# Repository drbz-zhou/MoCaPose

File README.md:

Reference:
@article{zhou2023mocapose,
  title={Mocapose: Motion capturing with textile-integrated capacitive sensors in loose-fitting smart garments},
  author={Zhou, Bo and Geissler, Daniel and Faulhaber, Marc and Gleiss, Clara Elisabeth and Zahn, Esther Friederike and Ray, Lala Shakti Swarup and Gamarra, David and Rey, Vitor Fortes and Suh, Sungho and Bian, Sizhen and others},
  journal={Proceedings of the ACM on Interactive, Mobile, Wearable and Ubiquitous Technologies},
  volume={7},
  number={1},
  pages={1--40},
  year={2023},
  publisher={ACM New York, NY, USA}
}

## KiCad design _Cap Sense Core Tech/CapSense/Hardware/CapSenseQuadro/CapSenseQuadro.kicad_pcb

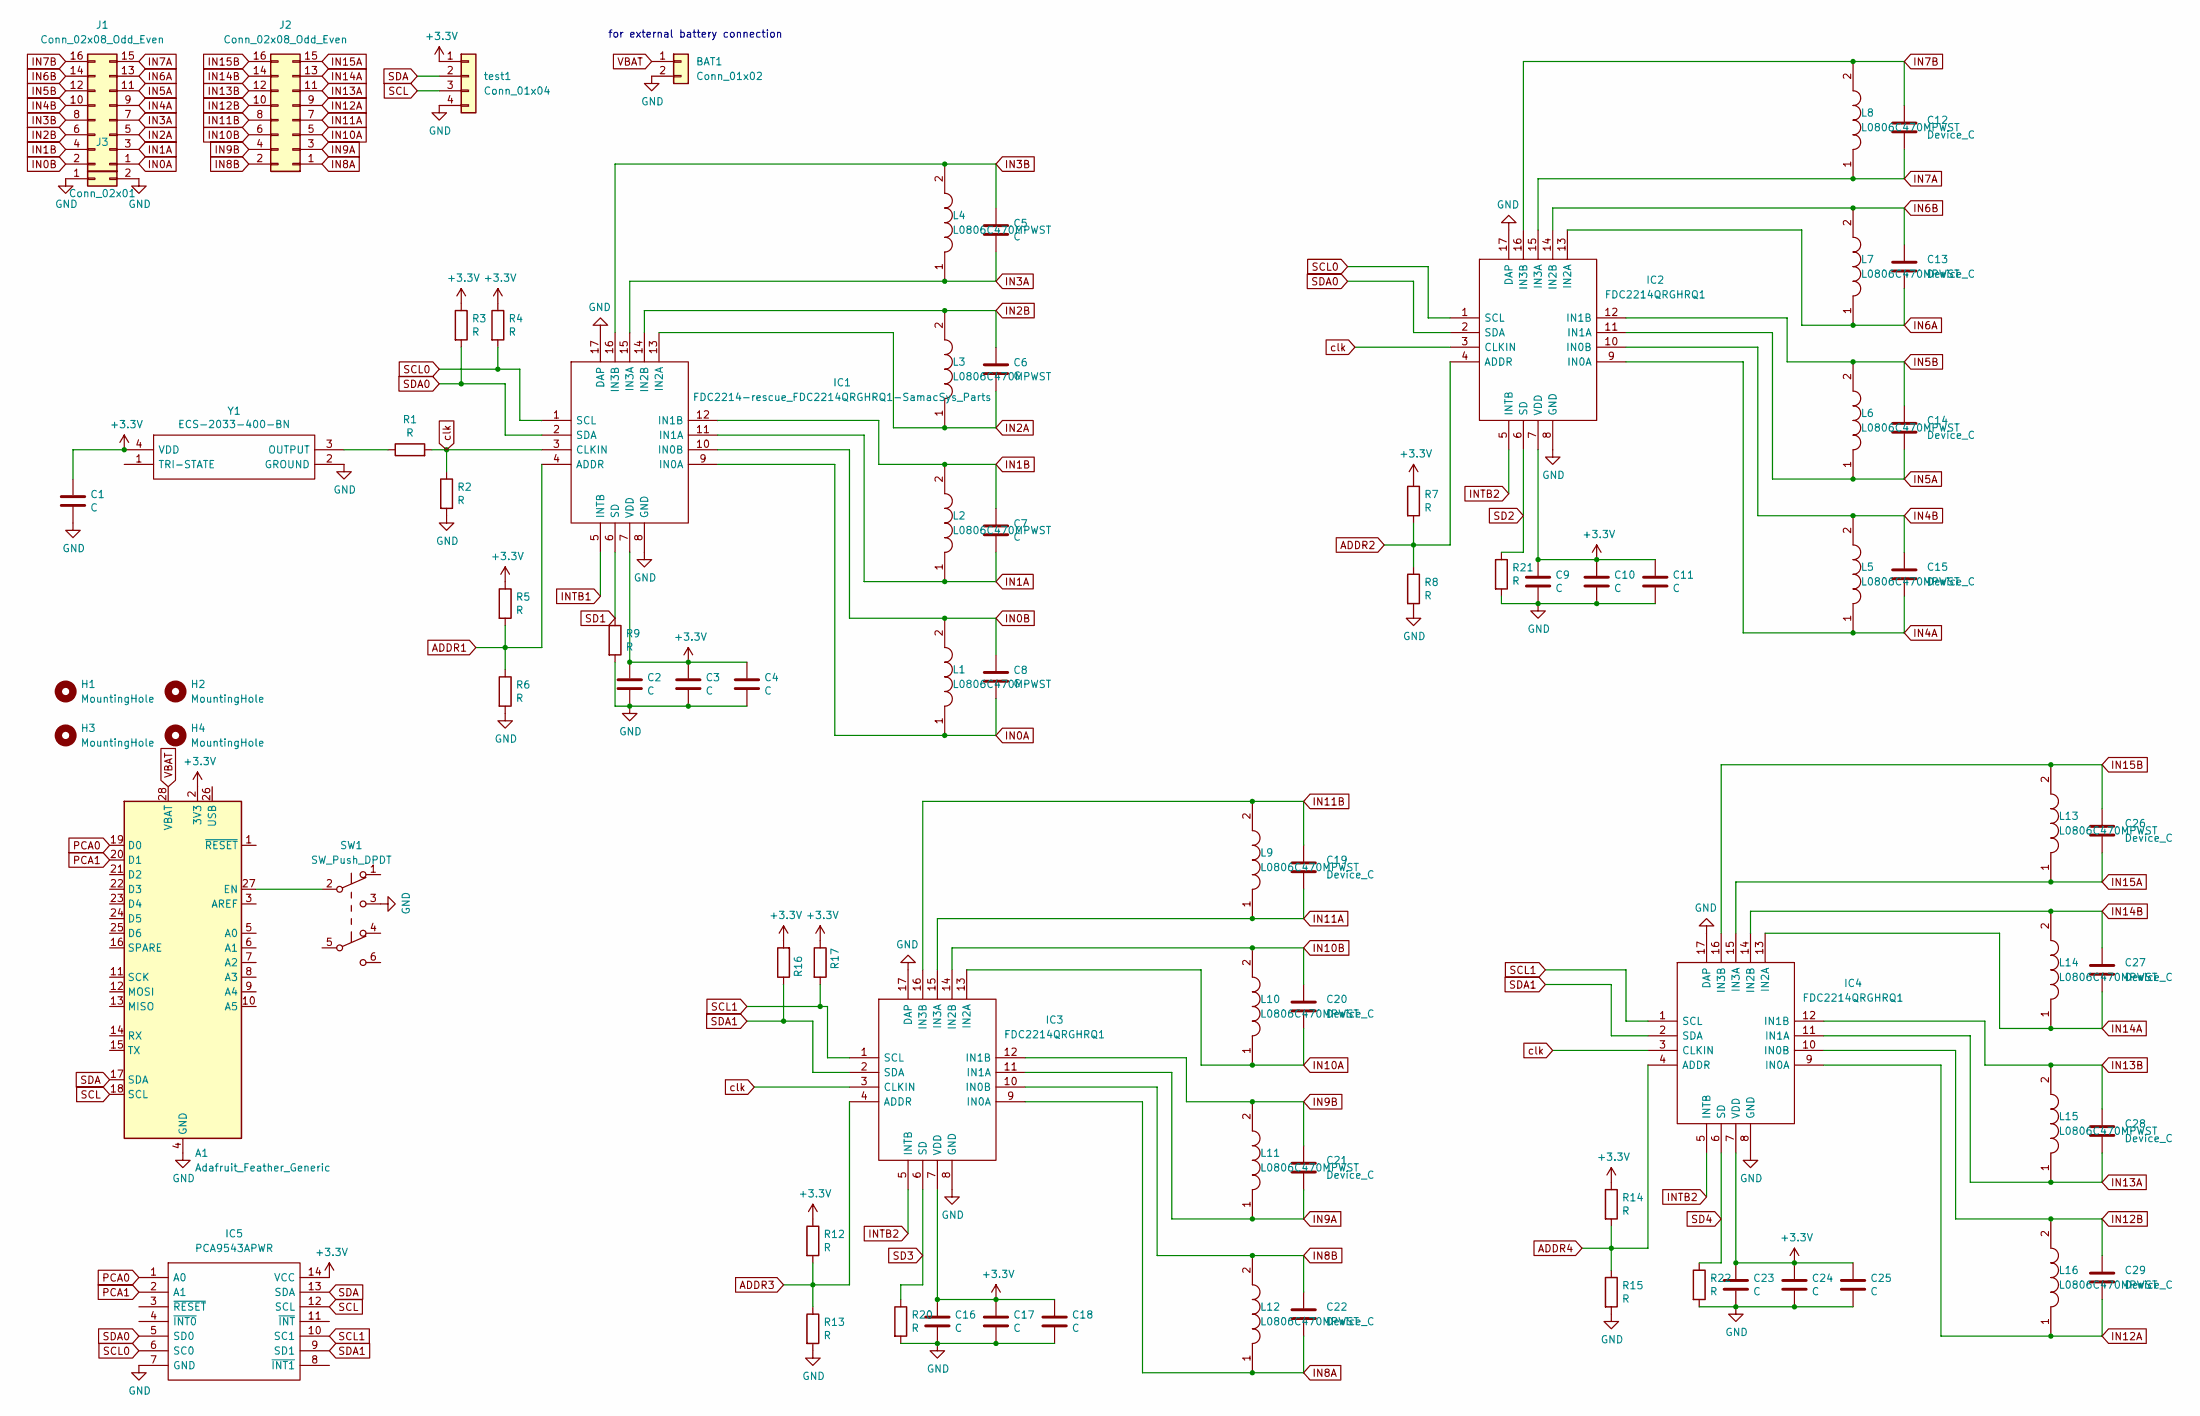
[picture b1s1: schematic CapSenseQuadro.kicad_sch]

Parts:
A1: Adafruit_Feather_Generic; Adafruit_Feather
BAT1: Conn_01x02; PinHeader_1x02_P2.54mm_Vertical
C1, C2, C3, C4, C5, C6, C7, C8, C9, C10, C11, C16, C17, C18, C23, C24, C25: C; C_0603_1608Metric
C12, C13, C14, C15, C19, C20, C21, C22, C26, C27, C28, C29: Device_C; C_0603_1608Metric
H1, H2, H3, H4: MountingHole; MountingHole_2.7mm_M2.5
IC1: FDC2214-rescue_FDC2214QRGHRQ1-SamacSys_Parts; FDC2214RGHR; Manufacturer_Part_Number FDC2214QRGHRQ1; Mouser Part Number 595-FDC2214QRGHRQ1
IC2, IC3, IC4: FDC2214QRGHRQ1; FDC2214RGHR; Manufacturer_Part_Number FDC2214QRGHRQ1; Mouser Part Number 595-FDC2214QRGHRQ1
IC5: PCA9543APWR; SOP65P640X120-14N; Mouser Part Number 595-PCA9543APWR
J1, J2: Conn_02x08_Odd_Even; PinHeader_2x08_P2.54mm_Horizontal
J3: Conn_02x01; PinHeader_2x01_P2.54mm_Horizontal
L1, L2, L3, L4, L5, L6, L7, L8, L9, L10, L11, L12, L13, L14, L15, L16: L0806C470MPWST; INDC2018X180N; Manufacturer_Part_Number L0806C470MPWST
R1, R2, R3, R4, R5, R6, R7, R8, R9, R12, R13, R14, R15, R16, R17, R20, R21, R22: R; R_0603_1608Metric_Pad0.98x0.95mm_HandSolder
SW1: SW_Push_DPDT; 2mm-DPDT
Y1: ECS-2033-400-BN; ECS2033400BN; Mouser Part Number 520-2033-400-BN
test1: Conn_01x04; PinHeader_1x04_P2.00mm_Vertical

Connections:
+3V3: A1.2 (3V3), C1.1, C2.1, C3.1, C4.1, C9.1, C10.1, C11.1, C16.1, C17.1, C18.1, C23.1, C24.1, C25.1, IC1.7 (VDD), IC2.7 (VDD), IC3.7 (VDD), IC4.7 (VDD), IC5.14 (VCC), R3.1, R4.1, R5.1, R7.1, R12.1, R14.1, R16.2, R17.1, Y1.4 (VDD), test1.1
ADDR1: IC1.4 (ADDR), R5.2, R6.1
ADDR2: IC2.4 (ADDR), R7.2, R8.1
ADDR3: IC3.4 (ADDR), R12.2, R13.1
ADDR4: IC4.4 (ADDR), R14.2, R15.1
GND: A1.4 (GND), BAT1.2, C1.2, C2.2, C3.2, C4.2, C9.2, C10.2, C11.2, C16.2, C17.2, C18.2, C23.2, C24.2, C25.2, IC1.8 (GND), IC1.17 (DAP), IC2.8 (GND), IC2.17 (DAP), IC3.8 (GND), IC3.17 (DAP), IC4.8 (GND), IC4.17 (DAP), IC5.7 (GND), J3.1, J3.2, R2.2, R6.2, R8.2, R9.2, R13.2, R15.2, R20.2, R21.2, R22.2, SW1.3 (C), Y1.2 (GROUND), test1.4
IN0A: C8.2, IC1.9 (IN0A), J1.1, L1.1
IN0B: C8.1, IC1.10 (IN0B), J1.2, L1.2
IN1A: C7.2, IC1.11 (IN1A), J1.3, L2.1
IN1B: C7.1, IC1.12 (IN1B), J1.4, L2.2
IN2A: C6.2, IC1.13 (IN2A), J1.5, L3.1
IN2B: C6.1, IC1.14 (IN2B), J1.6, L3.2
IN3A: C5.2, IC1.15 (IN3A), J1.7, L4.1
IN3B: C5.1, IC1.16 (IN3B), J1.8, L4.2
IN4A: C15.2, IC2.9 (IN0A), J1.9, L5.1
IN4B: C15.1, IC2.10 (IN0B), J1.10, L5.2
IN5A: C14.2, IC2.11 (IN1A), J1.11, L6.1
IN5B: C14.1, IC2.12 (IN1B), J1.12, L6.2
IN6A: C13.2, IC2.13 (IN2A), J1.13, L7.1
IN6B: C13.1, IC2.14 (IN2B), J1.14, L7.2
IN7A: C12.2, IC2.15 (IN3A), J1.15, L8.1
IN7B: C12.1, IC2.16 (IN3B), J1.16, L8.2
IN8A: C22.2, IC3.9 (IN0A), J2.1, L12.1
IN8B: C22.1, IC3.10 (IN0B), J2.2, L12.2
IN9A: C21.2, IC3.11 (IN1A), J2.3, L11.1
IN9B: C21.1, IC3.12 (IN1B), J2.4, L11.2
IN10A: C20.2, IC3.13 (IN2A), J2.5, L10.1
IN10B: C20.1, IC3.14 (IN2B), J2.6, L10.2
IN11A: C19.2, IC3.15 (IN3A), J2.7, L9.1
IN11B: C19.1, IC3.16 (IN3B), J2.8, L9.2
IN12A: C29.2, IC4.9 (IN0A), J2.9, L16.1
IN12B: C29.1, IC4.10 (IN0B), J2.10, L16.2
IN13A: C28.2, IC4.11 (IN1A), J2.11, L15.1
IN13B: C28.1, IC4.12 (IN1B), J2.12, L15.2
IN14A: C27.2, IC4.13 (IN2A), J2.13, L14.1
IN14B: C27.1, IC4.14 (IN2B), J2.14, L14.2
IN15A: C26.2, IC4.15 (IN3A), J2.15, L13.1
IN15B: C26.1, IC4.16 (IN3B), J2.16, L13.2
INTB1: IC1.5 (INTB)
INTB2: IC2.5 (INTB), IC3.5 (INTB), IC4.5 (INTB)
unnamed: A1.27 (EN), SW1.2 (B)
unnamed: R1.1, Y1.3 (OUTPUT)
PCA0: A1.19 (D0), IC5.1 (A0)
PCA1: A1.20 (D1), IC5.2 (A1)
SCL: A1.18 (SCL), IC5.12 (SCL), test1.3
SCL0: IC1.1 (SCL), IC2.1 (SCL), IC5.6 (SC0), R4.2
SCL1: IC3.1 (SCL), IC4.1 (SCL), IC5.10 (SC1), R17.2
SD1: IC1.6 (SD), R9.1
SD2: IC2.6 (SD), R21.1
SD3: IC3.6 (SD), R20.1
SD4: IC4.6 (SD), R22.1
SDA: A1.17 (SDA), IC5.13 (SDA), test1.2
SDA0: IC1.2 (SDA), IC2.2 (SDA), IC5.5 (SD0), R3.2
SDA1: IC3.2 (SDA), IC4.2 (SDA), IC5.9 (SD1), R16.1
VBAT: A1.28 (VBAT), BAT1.1
clk: IC1.3 (CLKIN), IC2.3 (CLKIN), IC3.3 (CLKIN), IC4.3 (CLKIN), R1.2, R2.1

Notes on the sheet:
for external battery connection

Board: 2 copper layers, 80 parts (5 on the bottom side), 55 nets, no tracks yet.

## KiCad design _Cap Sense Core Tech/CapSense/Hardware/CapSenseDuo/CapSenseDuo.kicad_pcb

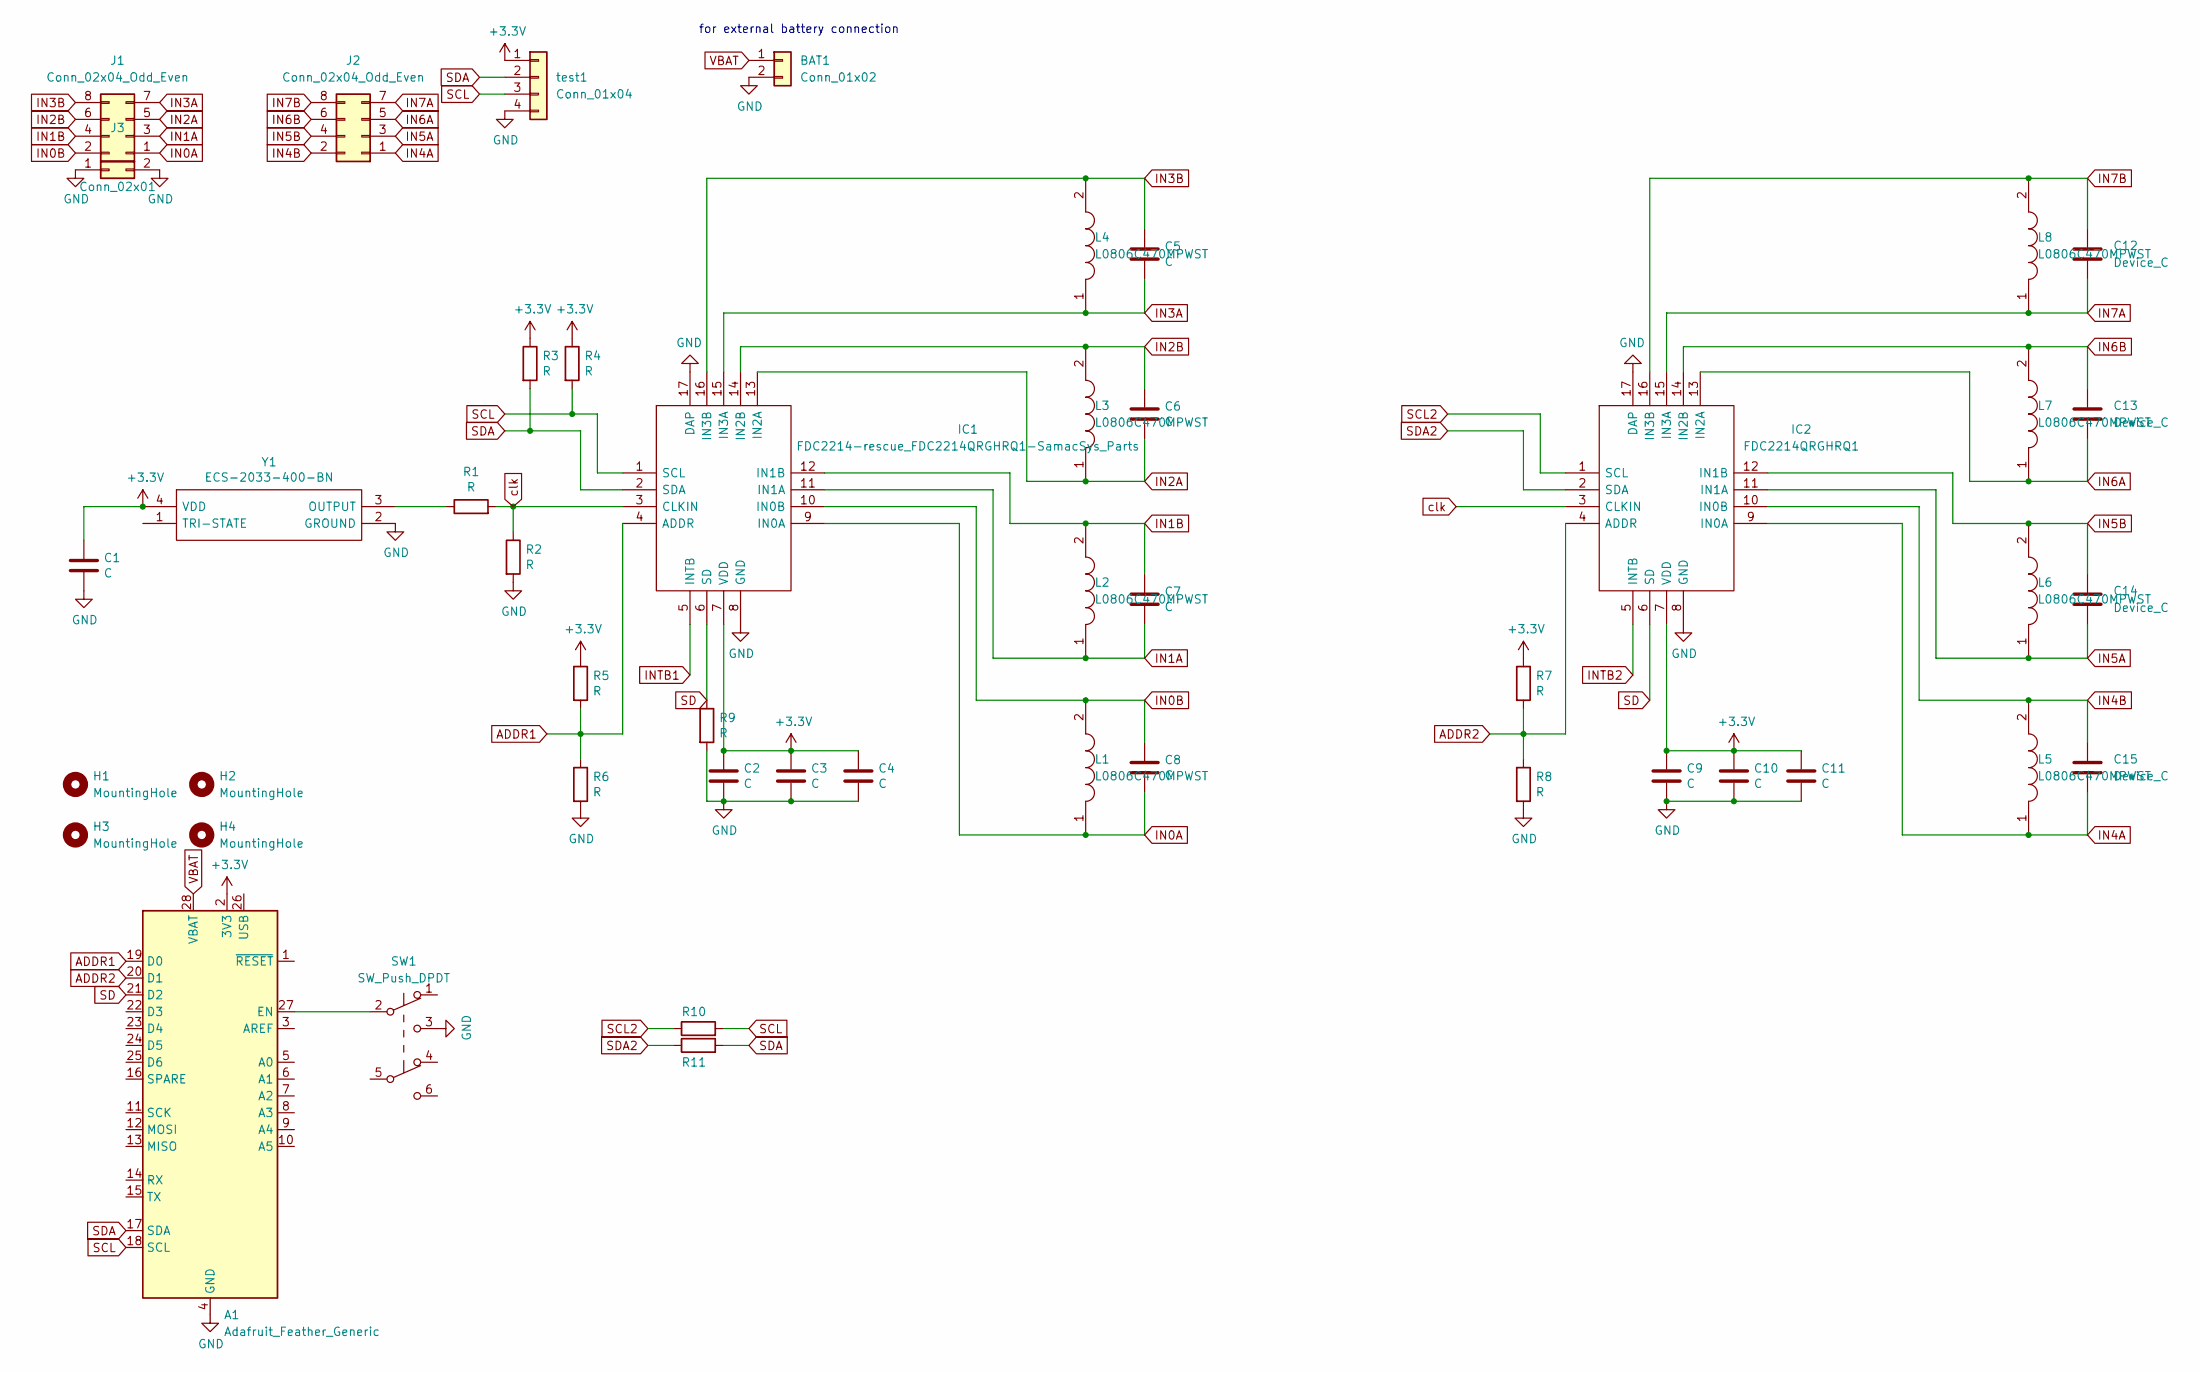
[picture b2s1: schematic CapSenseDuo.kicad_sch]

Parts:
A1: Adafruit_Feather_Generic; Adafruit_Feather
BAT1: Conn_01x02; PinHeader_1x02_P2.54mm_Vertical
C1, C2, C3, C4, C5, C6, C7, C8, C9, C10, C11: C; C_0603_1608Metric
C12, C13, C14, C15: Device_C; C_0603_1608Metric
H1, H2, H3, H4: MountingHole; MountingHole_2.7mm_M2.5
IC1: FDC2214-rescue_FDC2214QRGHRQ1-SamacSys_Parts; FDC2214RGHR; Manufacturer_Part_Number FDC2214QRGHRQ1; Mouser Part Number 595-FDC2214QRGHRQ1
IC2: FDC2214QRGHRQ1; FDC2214RGHR; Manufacturer_Part_Number FDC2214QRGHRQ1; Mouser Part Number 595-FDC2214QRGHRQ1
J1, J2: Conn_02x04_Odd_Even; PinHeader_2x04_P2.54mm_Horizontal
J3: Conn_02x01; PinHeader_2x01_P2.54mm_Horizontal
L1, L2, L3, L4, L5, L6, L7, L8: L0806C470MPWST; INDC2018X180N; Manufacturer_Part_Number L0806C470MPWST
R1, R2, R3, R4, R5, R6, R7, R8, R9, R10, R11: R; R_0603_1608Metric_Pad0.98x0.95mm_HandSolder
SW1: SW_Push_DPDT; 2mm-DPDT
Y1: ECS-2033-400-BN; ECS2033400BN; Mouser Part Number 520-2033-400-BN
test1: Conn_01x04; PinHeader_1x04_P2.00mm_Vertical

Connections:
+3V3: A1.2 (3V3), C1.1, R3.1, R4.1, R5.1, R7.1, Y1.4 (VDD), test1.1
ADDR1: A1.19 (D0), IC1.4 (ADDR), R5.2, R6.1
ADDR2: A1.20 (D1), IC2.4 (ADDR), R7.2, R8.1
GND: A1.4 (GND), BAT1.2, C1.2, C2.2, C3.2, C4.2, C9.2, C10.2, C11.2, IC1.8 (GND), IC1.17 (DAP), IC2.8 (GND), IC2.17 (DAP), J3.1, J3.2, R2.2, R6.2, R8.2, R9.2, SW1.3 (C), Y1.2 (GROUND), test1.4
IN0A: C8.2, IC1.9 (IN0A), J1.1, L1.1
IN0B: C8.1, IC1.10 (IN0B), J1.2, L1.2
IN1A: C7.2, IC1.11 (IN1A), J1.3, L2.1
IN1B: C7.1, IC1.12 (IN1B), J1.4, L2.2
IN2A: C6.2, IC1.13 (IN2A), J1.5, L3.1
IN2B: C6.1, IC1.14 (IN2B), J1.6, L3.2
IN3A: C5.2, IC1.15 (IN3A), J1.7, L4.1
IN3B: C5.1, IC1.16 (IN3B), J1.8, L4.2
IN4A: C15.2, IC2.9 (IN0A), J2.1, L5.1
IN4B: C15.1, IC2.10 (IN0B), J2.2, L5.2
IN5A: C14.2, IC2.11 (IN1A), J2.3, L6.1
IN5B: C14.1, IC2.12 (IN1B), J2.4, L6.2
IN6A: C13.2, IC2.13 (IN2A), J2.5, L7.1
IN6B: C13.1, IC2.14 (IN2B), J2.6, L7.2
IN7A: C12.2, IC2.15 (IN3A), J2.7, L8.1
IN7B: C12.1, IC2.16 (IN3B), J2.8, L8.2
INTB1: IC1.5 (INTB)
INTB2: IC2.5 (INTB)
unnamed: A1.27 (EN), SW1.2 (B)
unnamed: C2.1, C3.1, C4.1, IC1.7 (VDD)
unnamed: C9.1, C10.1, C11.1, IC2.7 (VDD)
unnamed: R1.1, Y1.3 (OUTPUT)
SCL: A1.18 (SCL), IC1.1 (SCL), R4.2, R10.2, test1.3
SCL2: IC2.1 (SCL), R10.1
SD: A1.21 (D2), IC1.6 (SD), IC2.6 (SD), R9.1
SDA: A1.17 (SDA), IC1.2 (SDA), R3.2, R11.2, test1.2
SDA2: IC2.2 (SDA), R11.1
VBAT: A1.28 (VBAT), BAT1.1
clk: IC1.3 (CLKIN), IC2.3 (CLKIN), R1.2, R2.1

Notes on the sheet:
for external battery connection

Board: 2 copper layers, 48 parts (5 on the bottom side), 31 nets, no tracks yet.

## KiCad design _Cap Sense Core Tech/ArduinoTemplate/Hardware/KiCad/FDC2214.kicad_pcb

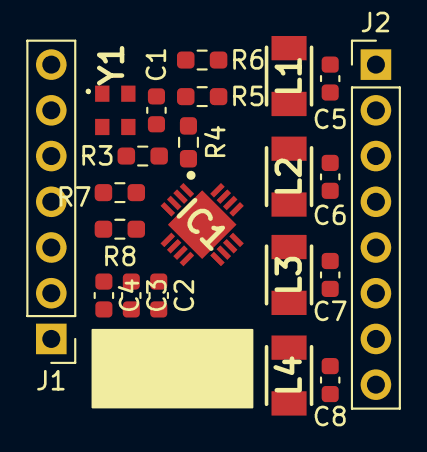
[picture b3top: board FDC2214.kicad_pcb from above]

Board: 2 copper layers, 22 parts (0 on the bottom side), 18 nets, no tracks yet.

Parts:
C1, C4: 0.01uF; C_0603_1608Metric
C2: 1uF; C_0603_1608Metric
C3: 0.1uF; C_0603_1608Metric
C5, C6, C7, C8: 33pF; C_0603_1608Metric
IC1: FDC2214QRGHRQ1; QFN50P400X400X80-17N
J1: Conn_01x07; PinHeader_1x07_P2.54mm_Vertical
J2: Conn_01x08; PinHeader_1x08_P2.54mm_Vertical
L1, L2, L3, L4: CMH322522-180KL; INDPM3225X240N
R3: 0; R_0603_1608Metric_Pad0.98x0.95mm_HandSolder
R4, R5, R6: 49; R_0603_1608Metric_Pad0.98x0.95mm_HandSolder
R7, R8: R; R_0603_1608Metric_Pad0.98x0.95mm_HandSolder
Y1: ECS-2033-400-BN; ECS2033400BN

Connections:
+3V3: C1.1, J1.5, R5.1, R6.1, R7.1, Y1.4
ADDR: IC1.4, J1.4, R7.2, R8.1
GND: C1.2, C2.2, C3.2, C4.2, IC1.8, IC1.17, J1.1, R4.2, R8.2, Y1.2
IN0A: C8.2, IC1.9, J2.8, L4.1
IN0B: C8.1, IC1.10, J2.7, L4.2
IN1A: C7.2, IC1.11, J2.6, L3.1
IN1B: C7.1, IC1.12, J2.5, L3.2
IN2A: C6.2, IC1.13, J2.4, L2.1
IN2B: C6.1, IC1.14, J2.3, L2.2
IN3A: C5.2, IC1.15, J2.2, L1.1
IN3B: C5.1, IC1.16, J2.1, L1.2
INTB: IC1.5, J1.3
unnamed: C2.1, C3.1, C4.1, IC1.7
unnamed: IC1.3, R3.2, R4.1
unnamed: R3.1, Y1.3
SCL: IC1.1, J1.7, R6.2
SD: IC1.6, J1.2
SDA: IC1.2, J1.6, R5.2

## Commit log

2021-11-08 references
2021-11-09 re organize
2021-12-01 modify layout
2021-12-06 adding BLE
2021-12-06 round sampling rate
2021-12-10 update FDC2214 library
2022-01-03 correct the repeat reading problem when reading two FDC2214 boards
2022-01-04 working 2 module BLE example
2022-01-10 Create Read2Sensors_BLE
2022-01-10 update Dashboard
2022-01-17 update WebUI
2022-01-17 clean up code
2022-01-17 Create FCD
2022-01-20 adding Reset button to WebUI
2022-01-20 WebUI performance improved
2022-01-20 WebUI switch from round to trunc
2022-01-24 update WebUI to fit split screen
2022-01-24 adding old Demo files
2022-02-17 fixing sampling rate calculations of WebUI
2022-02-22 Create a
2022-03-22 improve button usability
2022-04-11 update file naming and plot y axis
2022-06-09 pcb duo
2022-06-21 layout pre route
2022-06-23 place and route finished for CapDuo
2022-06-23 created Quadro project for future 4x FDC
2022-07-08 serial version for testing new module
2022-07-08 comment out SD/ADDR/INIT initializaers
2022-07-18 add BLE and structure folders
2022-07-25 update WebUI for new jacket
2023-03-16 autoscale graphs
2023-03-29 update WebUI and create Zip
2023-03-29 remove .DS_Store
2023-03-29 Remove Face Project

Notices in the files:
parts and their libraries:
Copyright 2021 Accelerated Designs. All rights reserved.
